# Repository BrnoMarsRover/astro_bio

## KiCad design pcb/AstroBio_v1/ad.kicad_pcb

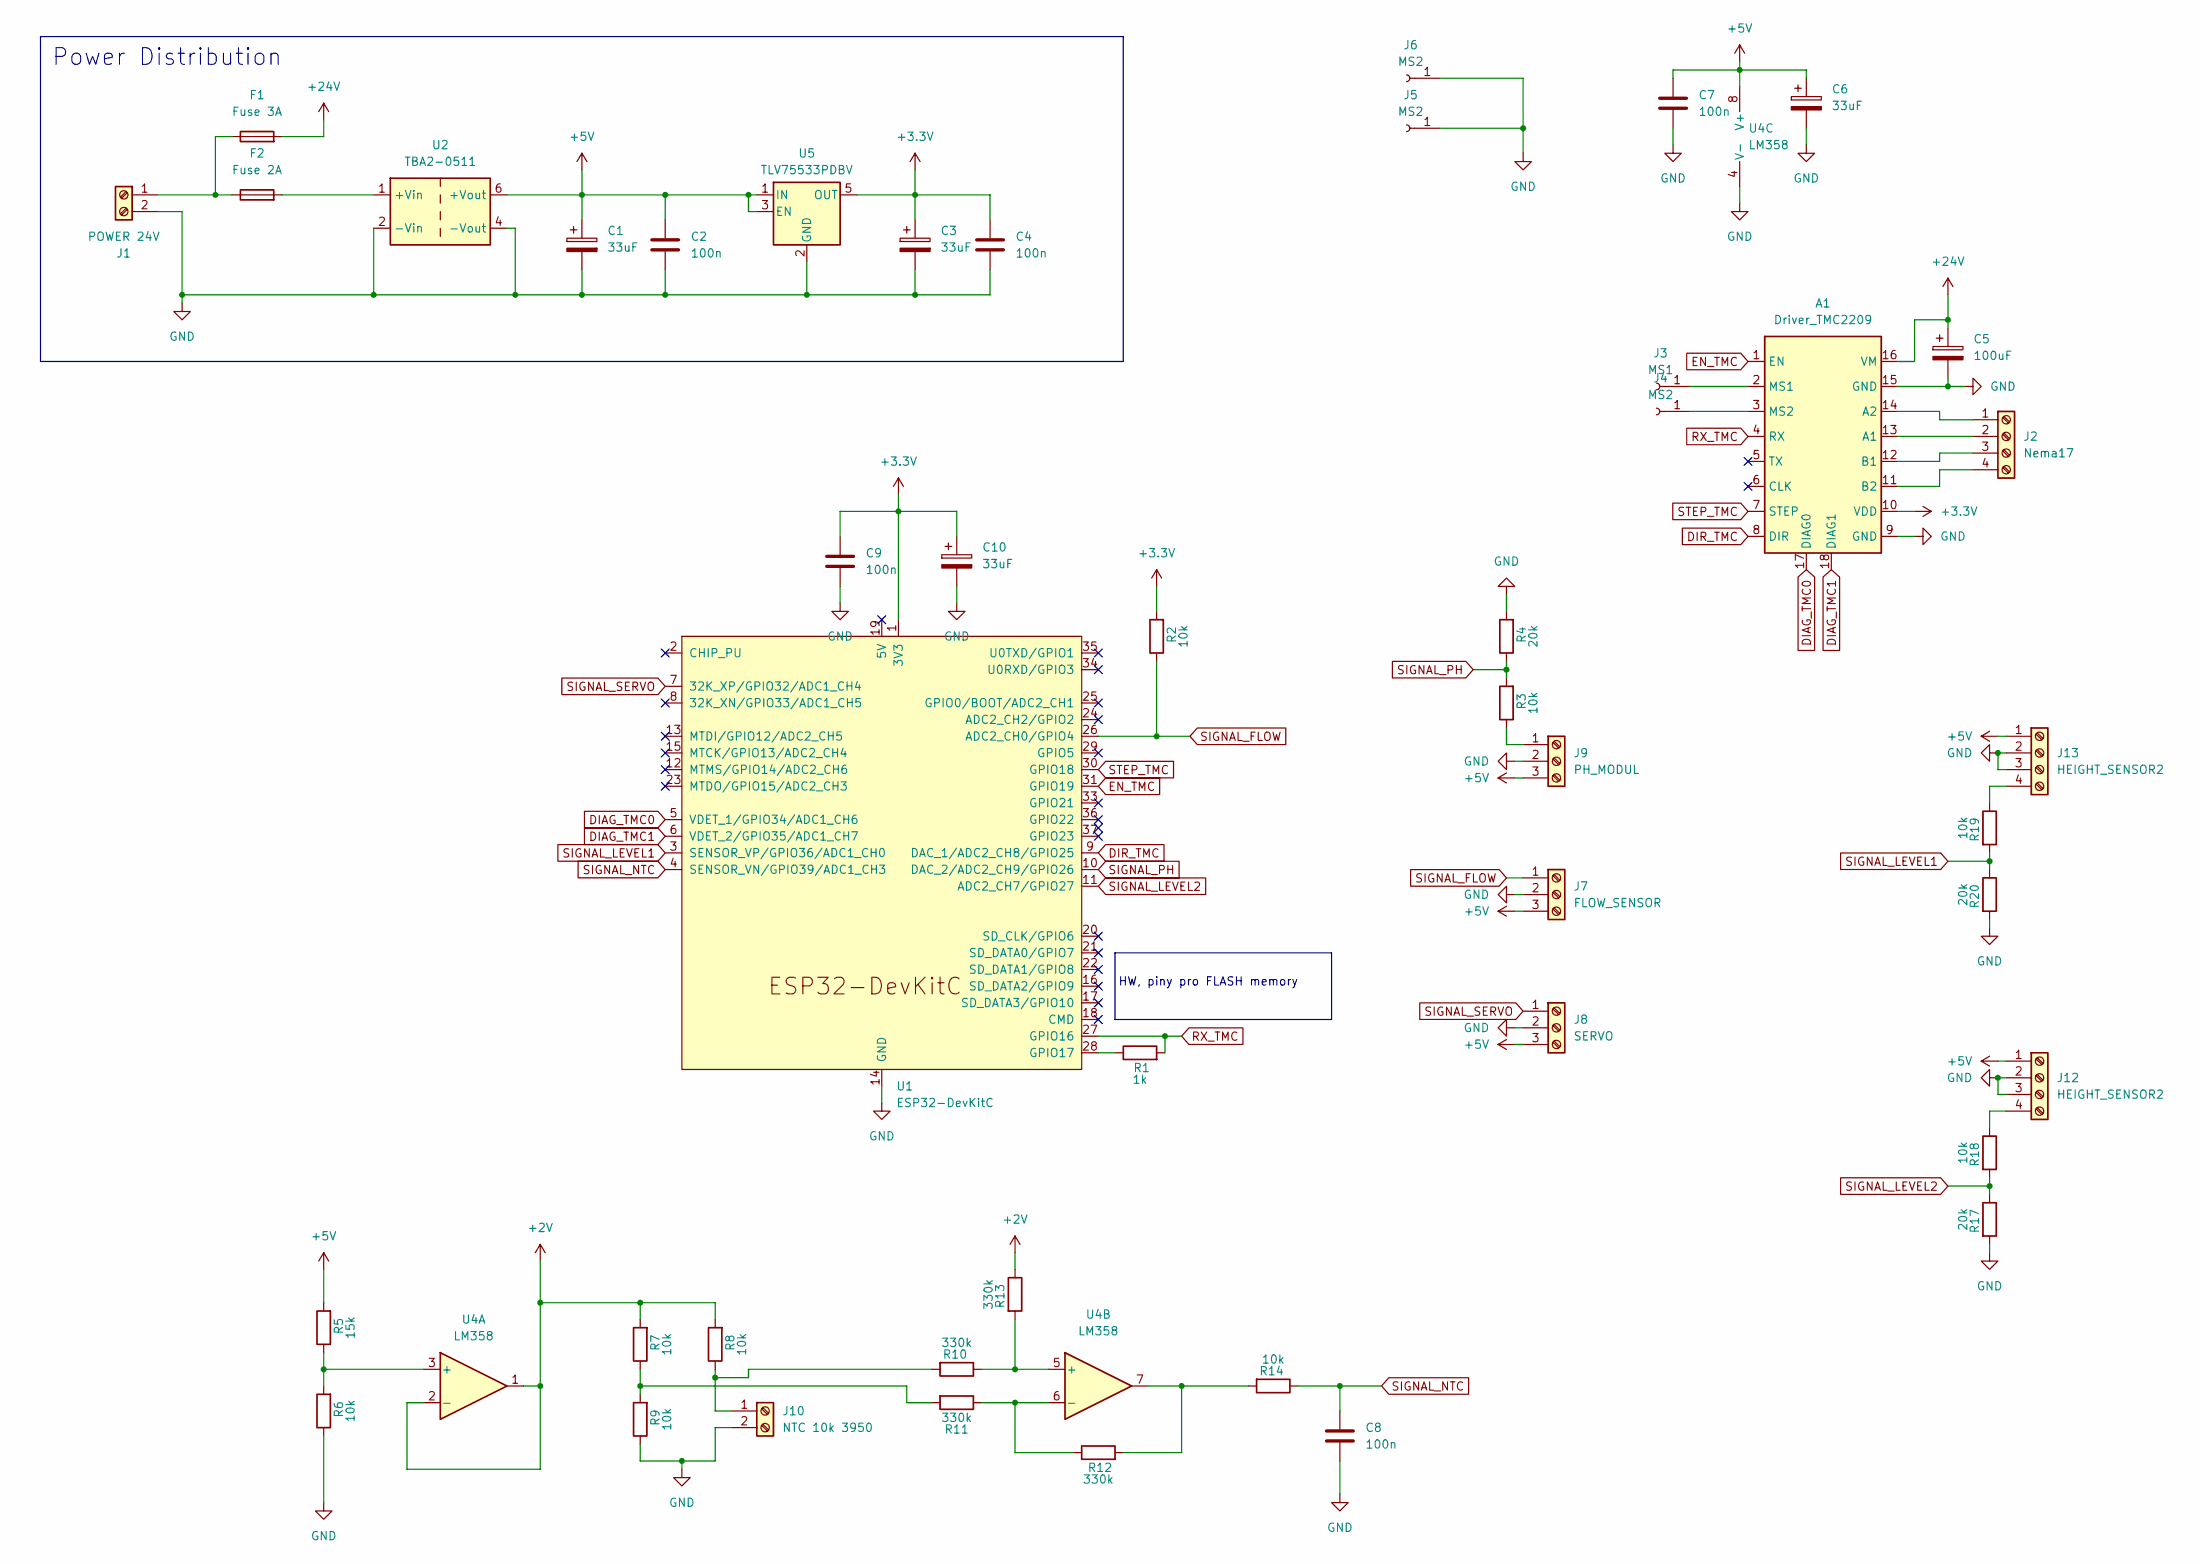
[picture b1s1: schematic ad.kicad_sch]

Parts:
A1: Driver_TMC2209; Pololu_Breakout-16_15.2x20.3mm
C1, C3: 33uF; CP_Radial_D8.0mm_P3.50mm
C2, C4, C7, C8, C9: 100n; C_1206_3216Metric_Pad1.33x1.80mm_HandSolder
C5: 100uF; CP_Radial_D8.0mm_P3.50mm
C6, C10: 33uF; CP_Radial_D5.0mm_P2.00mm
F1: Fuse 3A; fuseHolderATO
F2: Fuse 2A; fuseHolderATO
J1: POWER 24V; DEANS
J2: Nema17; JST_XH_B4B-XH-A_1x04_P2.50mm_Vertical
J3: MS1; Pin_D1.0mm_L10.0mm
J4, J5, J6: MS2; Pin_D1.0mm_L10.0mm
J7: FLOW_SENSOR; JST_XH_B3B-XH-A_1x03_P2.50mm_Vertical
J8: SERVO; JST_XH_B3B-XH-A_1x03_P2.50mm_Vertical
J9: PH_MODUL; JST_XH_B3B-XH-A_1x03_P2.50mm_Vertical
J10: NTC 10k 3950; JST_XH_B2B-XH-A_1x02_P2.50mm_Vertical
J12, J13: HEIGHT_SENSOR2; JST_XH_B4B-XH-A_1x04_P2.50mm_Vertical
R1: 1k; R_1206_3216Metric
R2, R3, R6, R7, R8, R9, R14, R18, R19: 10k; R_1206_3216Metric
R4, R17, R20: 20k; R_1206_3216Metric
R5: 15k; R_1206_3216Metric
R10, R11, R12, R13: 330k; R_1206_3216Metric
U1: ESP32-DevKitC
U2: TBA2-0511; dcdc_menic
U4: LM358; DIP-8_W7.62mm
U5: TLV75533PDBV; SOT-23-5

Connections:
+2V: R7.2, R8.2, R13.1, U4.1, U4.2 (-)
+3.3V: A1.10 (VDD), C3.1, C4.1, C9.1, C10.1, R2.2, U1.1 (3V3), U5.5 (OUT)
+5V: C1.1, C2.1, C6.1, C7.1, J7.3, J8.3, J9.3, J12.1, J13.1, R5.2, U2.6 (+Vout), U4.8 (V+), U5.1 (IN), U5.3 (EN)
+24V: A1.16 (VM), C5.1, F1.2
DIAG_TMC0: A1.17 (DIAG0), U1.5 (VDET_1/GPIO34/ADC1_CH6)
DIAG_TMC1: A1.18 (DIAG1), U1.6 (VDET_2/GPIO35/ADC1_CH7)
DIR_TMC: A1.8 (DIR), U1.9 (DAC_1/ADC2_CH8/GPIO25)
EN_TMC: A1.1 (EN), U1.31 (GPIO19)
GND: A1.9 (GND), A1.15 (GND), C1.2, C2.2, C3.2, C4.2, C5.2, C6.2, C7.2, C8.2, C9.2, C10.2, J1.2, J5.1 (Pin_1_1), J6.1 (Pin_1_1), J7.2, J8.2, J9.2, J10.2, J12.2, J12.3, J13.2, J13.3, R4.2, R6.1, R9.1, R17.2, R20.2, U1.14 (GND), U1.32 (GND), U1.38 (GND), U2.2 (-Vin), U2.4 (-Vout), U4.4 (V-), U5.2 (GND)
unnamed: A1.13 (A1), J2.2
unnamed: A1.14 (A2), J2.1
unnamed: A1.12 (B1), J2.3
unnamed: A1.11 (B2), J2.4
unnamed: A1.2 (MS1), J3.1 (Pin_1_1)
unnamed: A1.3 (MS2), J4.1 (Pin_1_1)
unnamed: F1.1, F2.1, J1.1
unnamed: J9.1, R3.1
unnamed: J10.1, R8.1, R10.2
unnamed: J12.4, R18.1
unnamed: J13.4, R19.1
unnamed: R7.1, R9.2, R11.2
unnamed: R12.2, R14.2, U4.7
unnamed: R1.1, U1.28 (GPIO17)
unnamed: F2.2, U2.1 (+Vin)
unnamed: R5.1, R6.2, U4.3 (+)
unnamed: R10.1, R13.2, U4.5 (+)
unnamed: R11.1, R12.1, U4.6 (-)
RX_TMC: A1.4 (RX), R1.2, U1.27 (GPIO16)
SIGNAL_FLOW: J7.1, R2.1, U1.26 (ADC2_CH0/GPIO4)
SIGNAL_LEVEL1: R19.2, R20.1, U1.3 (SENSOR_VP/GPIO36/ADC1_CH0)
SIGNAL_LEVEL2: R17.1, R18.2, U1.11 (ADC2_CH7/GPIO27)
SIGNAL_NTC: C8.1, R14.1, U1.4 (SENSOR_VN/GPIO39/ADC1_CH3)
SIGNAL_PH: R3.2, R4.1, U1.10 (DAC_2/ADC2_CH9/GPIO26)
SIGNAL_SERVO: J8.1, U1.7 (32K_XP/GPIO32/ADC1_CH4)
STEP_TMC: A1.7 (STEP), U1.30 (GPIO18)

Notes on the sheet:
HW, piny pro FLASH memory
Power Distribution

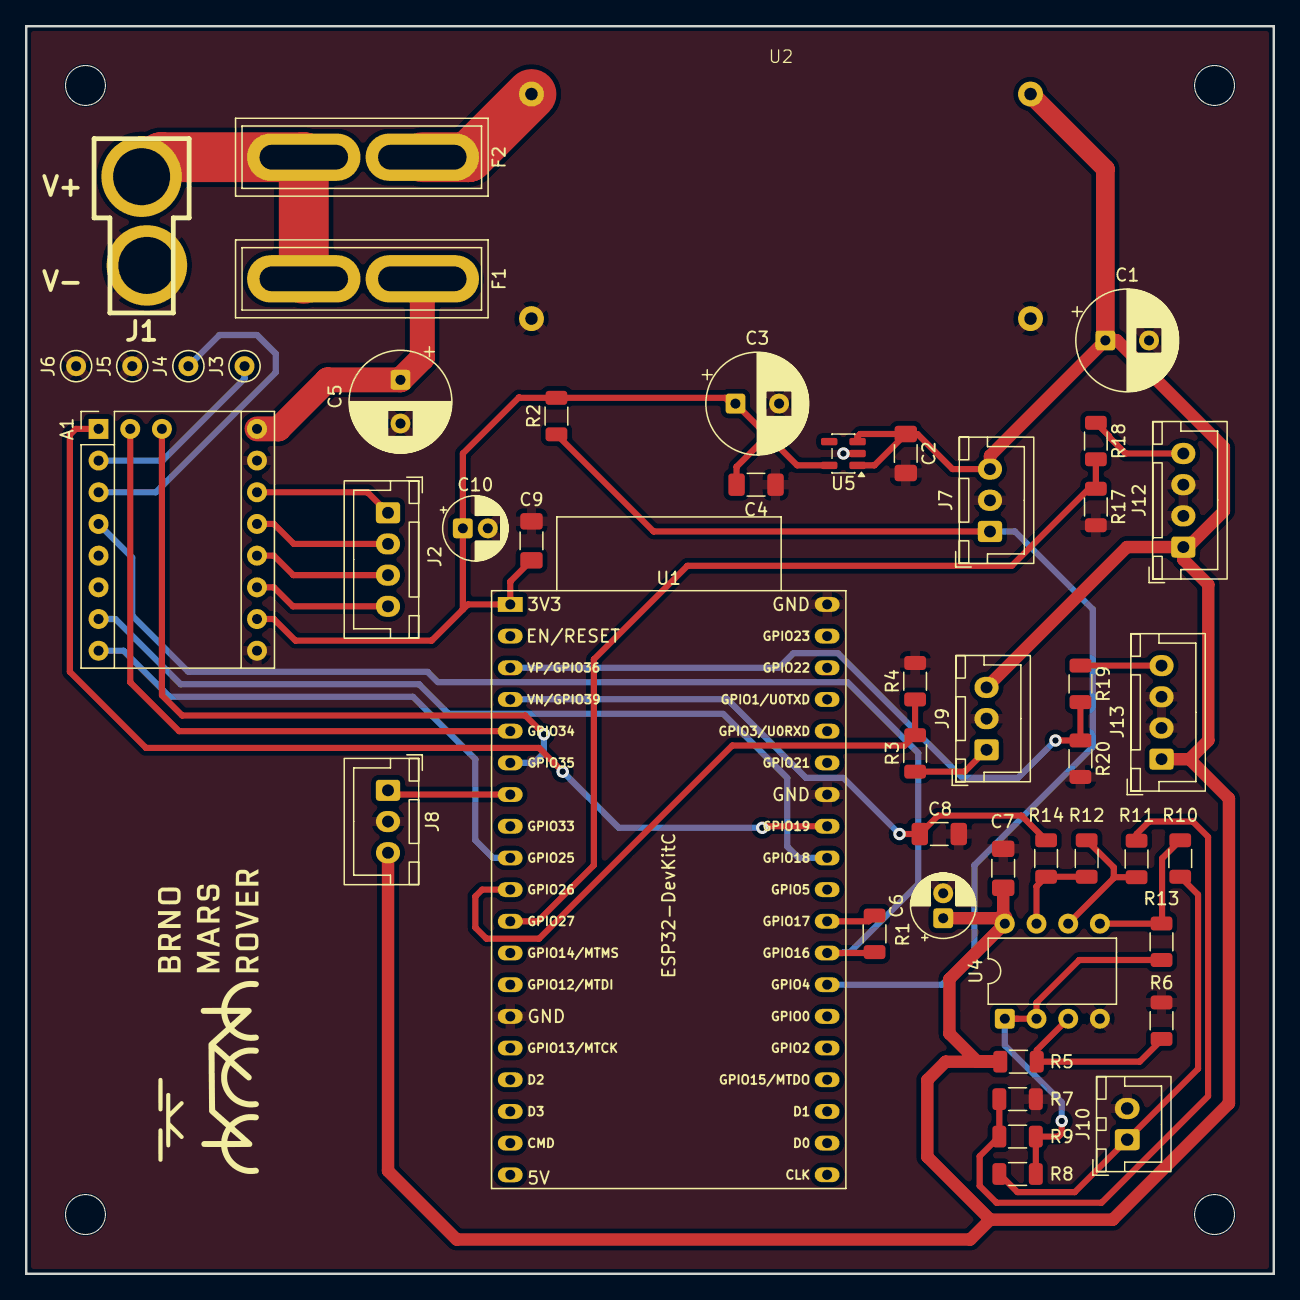
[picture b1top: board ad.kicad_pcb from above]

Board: 2 copper layers, 100.0 x 100.0 mm, 47 parts (0 on the bottom side), 35 nets.

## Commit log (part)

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2026-06-23 Added v1 of pcb
2026-06-26 Flip the ESP32 around and generate gerbers
2026-06-26 change the LDO for a smaller one
